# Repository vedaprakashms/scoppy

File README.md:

# scoppy
PI Pico ossciloscope using simple components

The project contains multiple directory, each with its own kind of Scopy, i.e Surface mountable, through hole, etc...

The Directory names are self explanatory. 

# IMAGES

## Scoppy SMD Single sided PCB

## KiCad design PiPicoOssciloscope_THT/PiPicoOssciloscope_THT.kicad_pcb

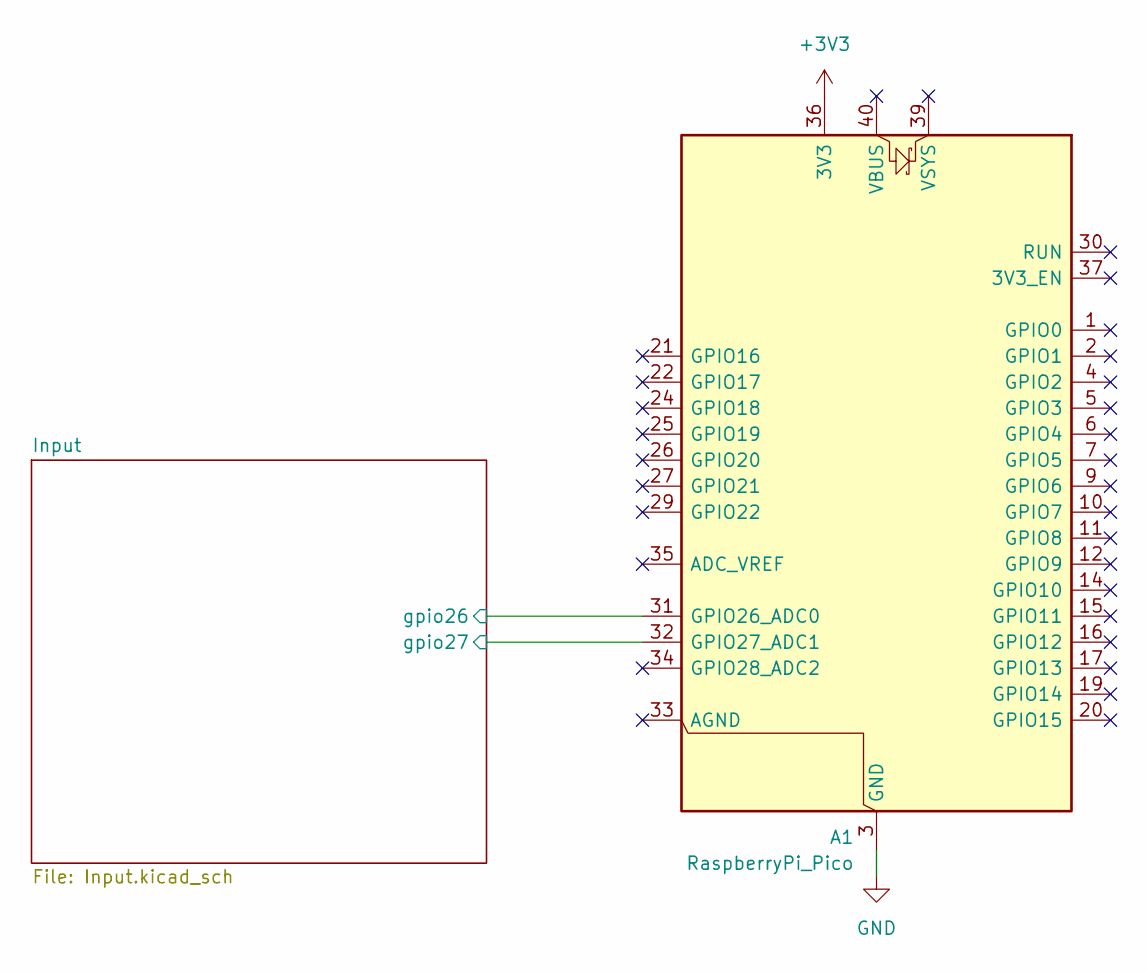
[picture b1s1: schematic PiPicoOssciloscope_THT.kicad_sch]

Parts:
A1: RaspberryPi_Pico; RaspberryPi_Pico_Common_THT

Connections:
+3V3: A1.36 (3V3); also elsewhere on the board
/Input/gpio26: A1.31 (GPIO26_ADC0); also elsewhere on the board
/Input/gpio27: A1.32 (GPIO27_ADC1); also elsewhere on the board
GND: A1.3 (GND), A1.8 (GND), A1.13 (GND), A1.18 (GND), A1.23 (GND), A1.28 (GND), A1.38 (GND); also elsewhere on the board

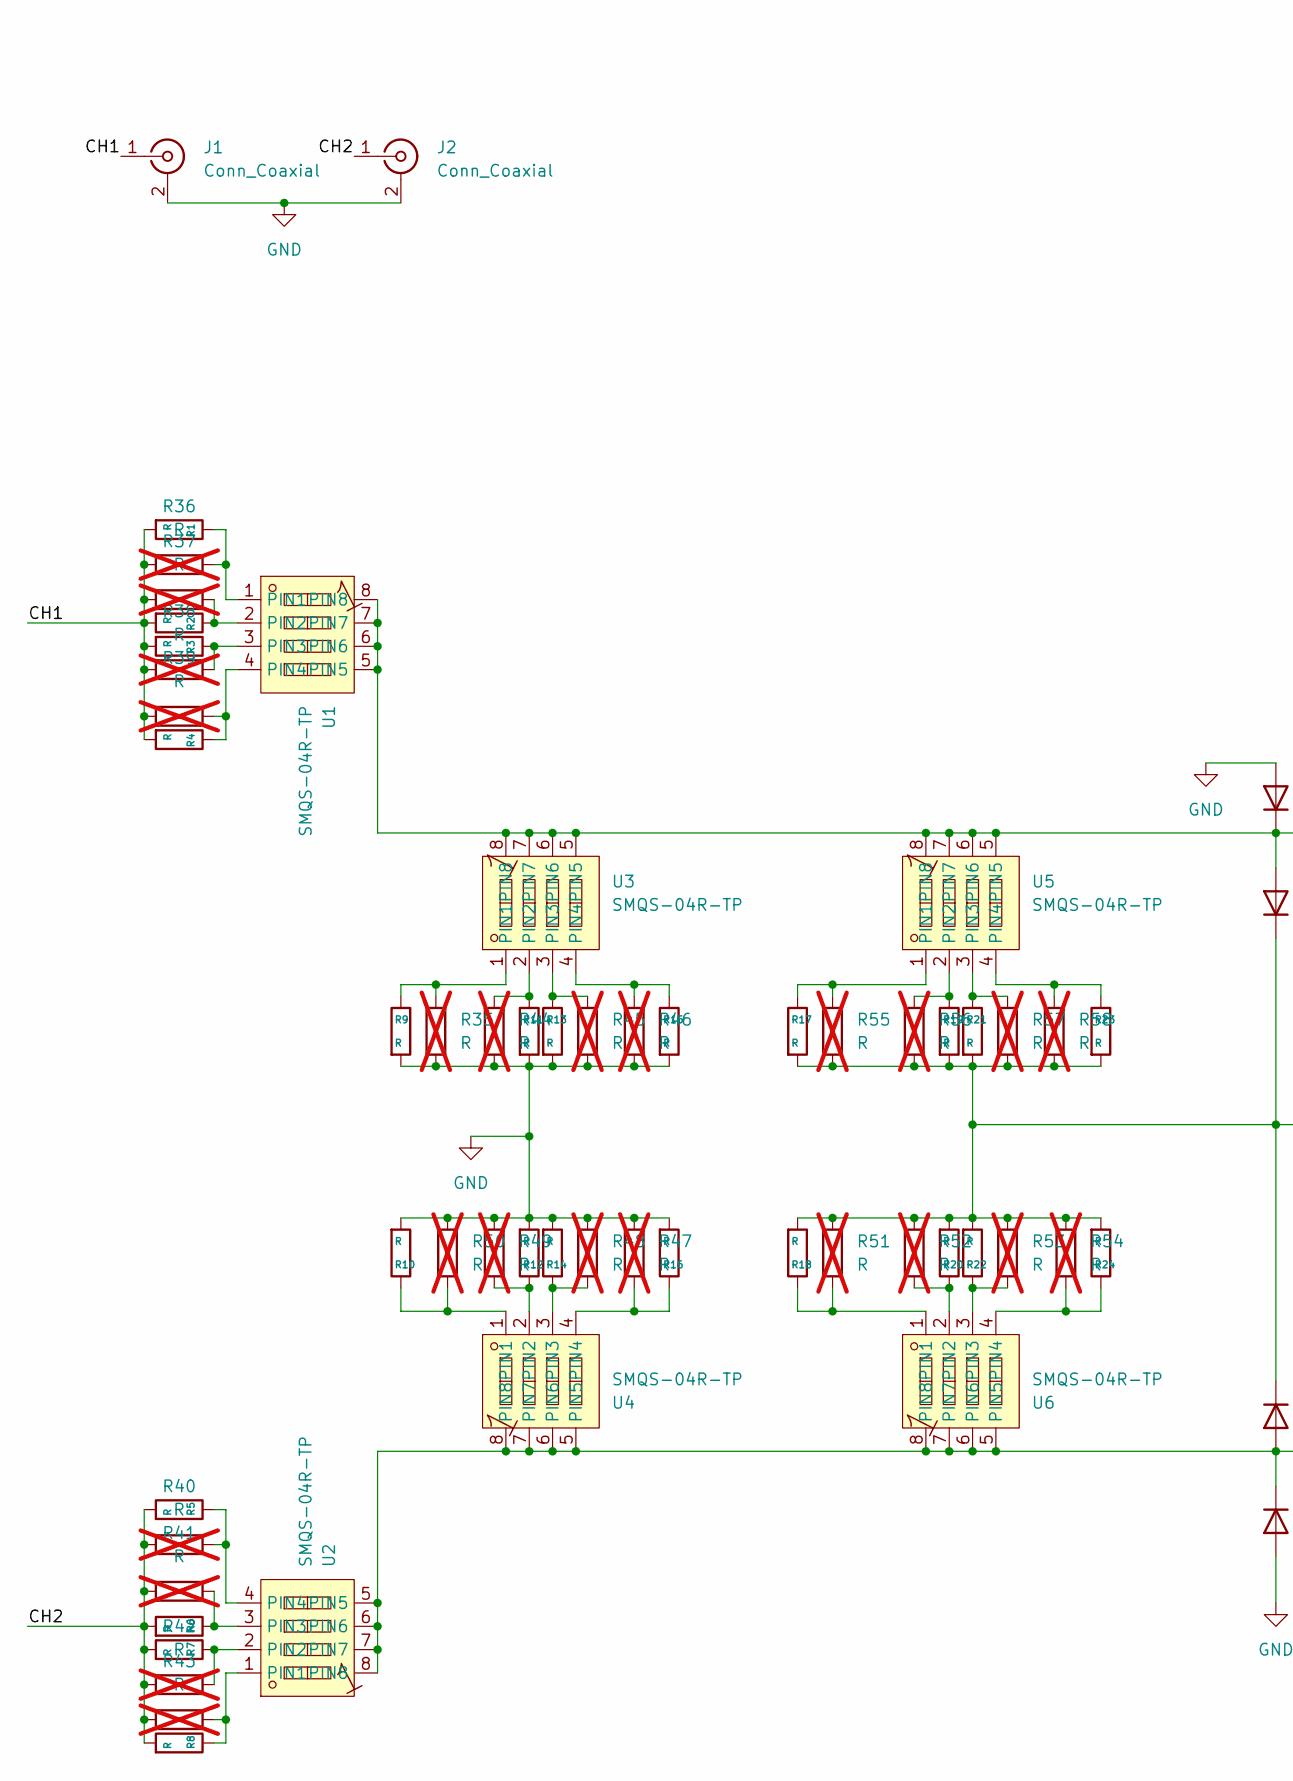
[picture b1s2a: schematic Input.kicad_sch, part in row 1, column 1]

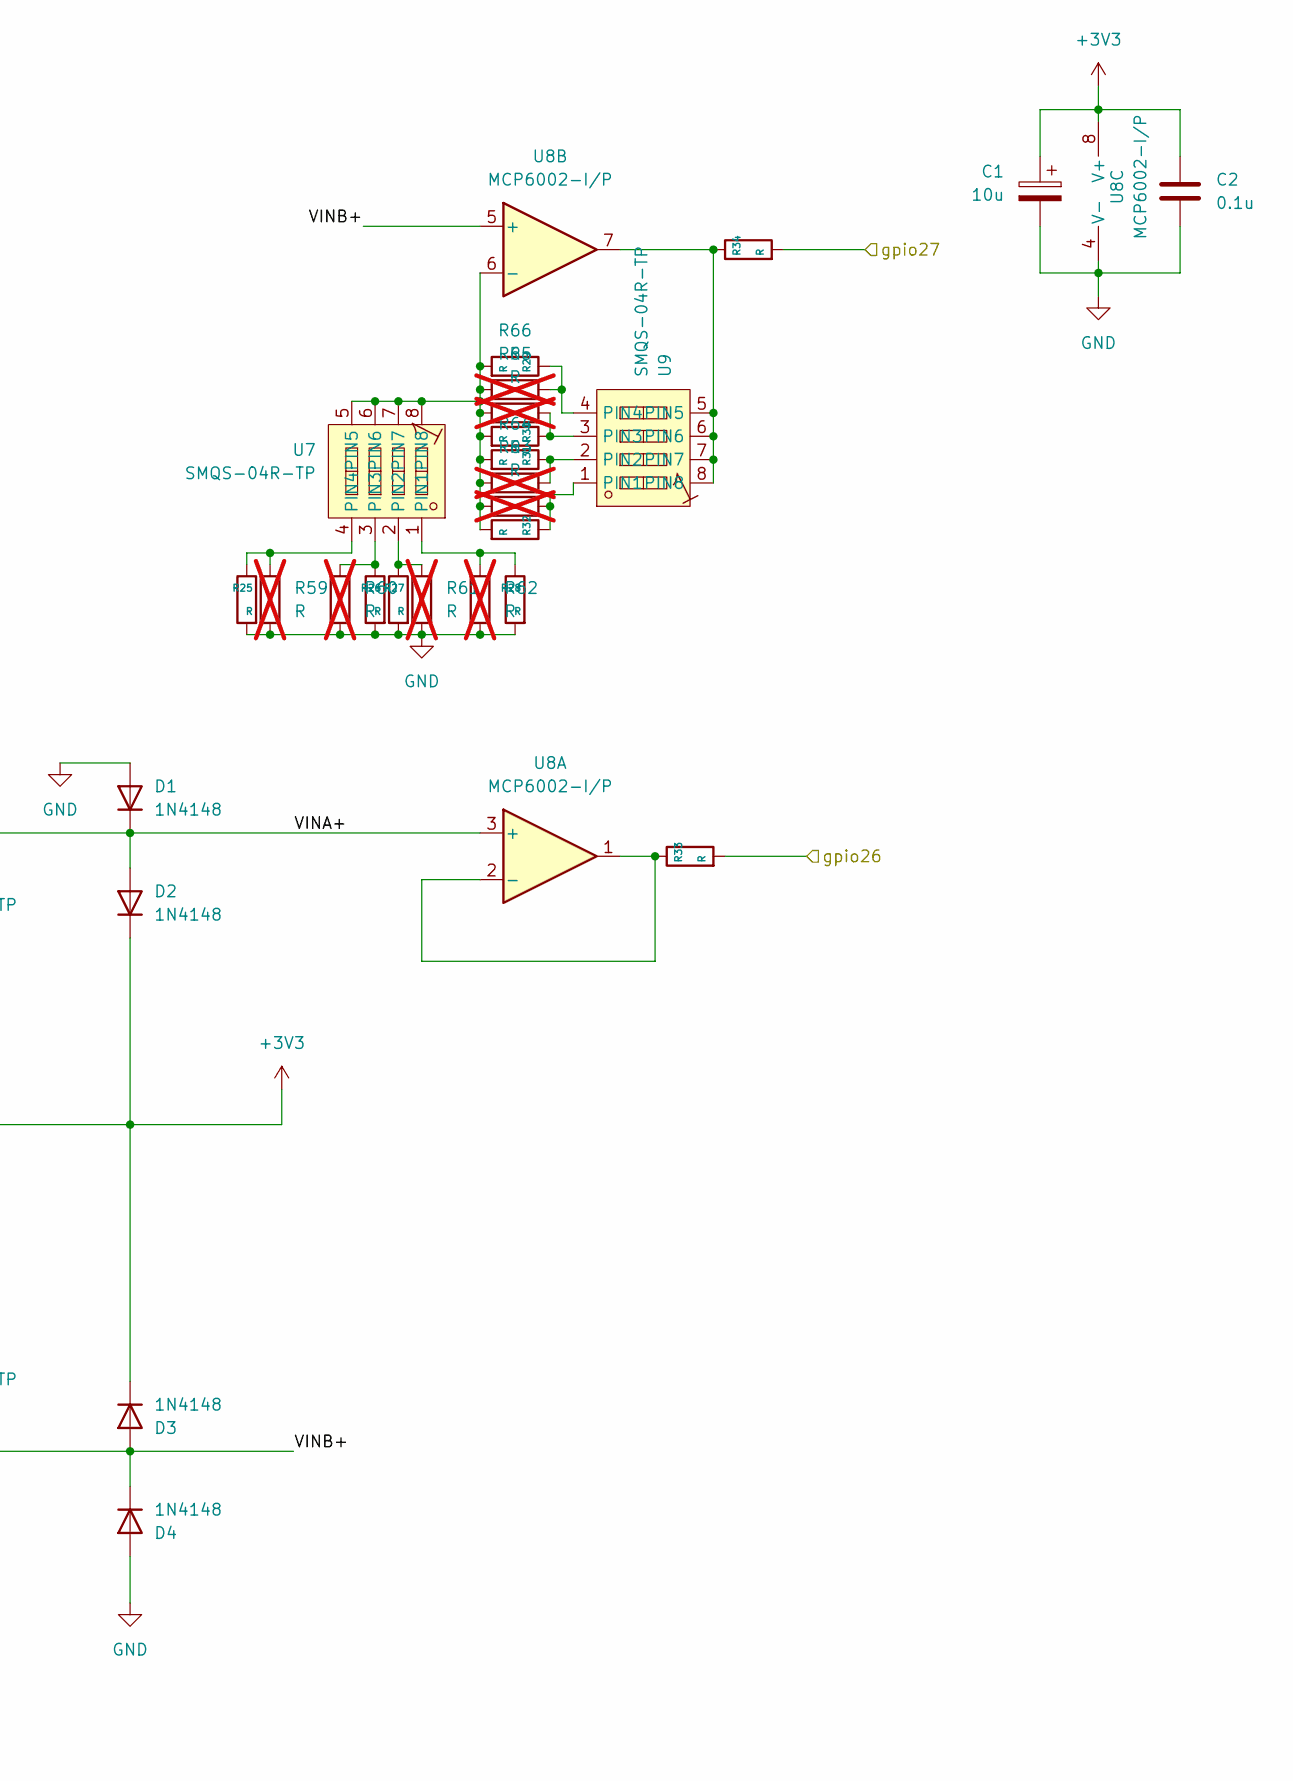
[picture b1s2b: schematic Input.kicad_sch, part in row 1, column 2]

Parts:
C1: 10u; CP_Radial_D10.0mm_P2.50mm
C2: 0.1u; C_Disc_D3.0mm_W1.6mm_P2.50mm
D1, D2, D3, D4: 1N4148; D_DO-35_SOD27_P7.62mm_Horizontal
J1, J2: Conn_Coaxial; BNC_Amphenol_B6252HB-NPP3G-50_Horizontal
R1, R2, R3, R4, R5, R6, R7, R8, R9, R10, R11, R12, R13, R14, R15, R16, R17, R18, R19, R20, R21, R22, R23, R24, R25, R26, R27, R28, R29, R30, R31, R32, R33, R34: R; R_Axial_DIN0204_L3.6mm_D1.6mm_P7.62mm_Horizontal
R35, R36, R37, R38, R39, R40, R41, R42, R43, R44, R45, R46, R47, R48, R49, R50, R51, R52, R53, R54, R55, R56, R57, R58, R59, R60, R61, R62, R63, R64, R65, R66: R; R_0805_2012Metric_Pad1.20x1.40mm_HandSolder; not fitted
U1, U2, U3, U4, U5, U6, U7, U9: SMQS-04R-TP; SW-TH_8P-P2.54_SMQS-04R-TP; MPN SMQS-04R-TP; LCSC Part C5299505
U8: MCP6002-I/P; DIP-8_W7.62mm_Socket_LongPads

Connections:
+3V3: C1.1, C2.1, D2.1 (K), D3.1 (K), R17.2, R18.2, R19.2, R20.2, R21.2, R22.2, R23.2, R24.2, R51.1, R52.1, R53.1, R54.1, R55.2, R56.2, R57.2, R58.2, U8.8 (V+); also elsewhere on the board
/Input/CH1: J1.1 (In), R1.2, R2.2, R3.2, R4.2, R36.1, R37.1, R38.1, R39.1
/Input/CH2: J2.1 (In), R5.2, R6.2, R7.2, R8.2, R40.1, R41.1, R42.1, R43.1
/Input/VINA+: D1.1 (K), D2.2 (A), U1.5 (PIN5), U1.6 (PIN6), U1.7 (PIN7), U1.8 (PIN8), U3.5 (PIN5), U3.6 (PIN6), U3.7 (PIN7), U3.8 (PIN8), U5.5 (PIN5), U5.6 (PIN6), U5.7 (PIN7), U5.8 (PIN8), U8.3 (+)
/Input/VINB+: D3.2 (A), D4.1 (K), U2.5 (PIN5), U2.6 (PIN6), U2.7 (PIN7), U2.8 (PIN8), U4.5 (PIN5), U4.6 (PIN6), U4.7 (PIN7), U4.8 (PIN8), U6.5 (PIN5), U6.6 (PIN6), U6.7 (PIN7), U6.8 (PIN8), U8.5 (+)
/Input/gpio26: R33.2; also elsewhere on the board
/Input/gpio27: R34.2; also elsewhere on the board
GND: C1.2, C2.2, D1.2 (A), D4.2 (A), J1.2 (Ext), J2.2 (Ext), R9.2, R10.2, R11.2, R12.2, R13.2, R14.2, R15.2, R16.2, R25.2, R26.2, R27.2, R28.2, R35.2, R44.2, R45.2, R46.2, R47.1, R48.1, R49.1, R50.1, R59.2, R60.2, R61.2, R62.2, U8.4 (V-); also elsewhere on the board
unnamed: R1.1, R36.2, U1.1 (PIN1)
unnamed: R2.1, R37.2, U1.2 (PIN2)
unnamed: R3.1, R38.2, U1.3 (PIN3)
unnamed: R4.1, R39.2, U1.4 (PIN4)
unnamed: R8.1, R43.2, U2.1 (PIN1)
unnamed: R7.1, R42.2, U2.2 (PIN2)
unnamed: R6.1, R41.2, U2.3 (PIN3)
unnamed: R5.1, R40.2, U2.4 (PIN4)
unnamed: R9.1, R35.1, U3.1 (PIN1)
unnamed: R11.1, R44.1, U3.2 (PIN2)
unnamed: R13.1, R45.1, U3.3 (PIN3)
unnamed: R15.1, R46.1, U3.4 (PIN4)
unnamed: R10.1, R50.2, U4.1 (PIN1)
unnamed: R12.1, R49.2, U4.2 (PIN2)
unnamed: R14.1, R48.2, U4.3 (PIN3)
unnamed: R16.1, R47.2, U4.4 (PIN4)
unnamed: R17.1, R55.1, U5.1 (PIN1)
unnamed: R19.1, R56.1, U5.2 (PIN2)
unnamed: R21.1, R57.1, U5.3 (PIN3)
unnamed: R23.1, R58.1, U5.4 (PIN4)
unnamed: R18.1, R51.2, U6.1 (PIN1)
unnamed: R20.1, R52.2, U6.2 (PIN2)
unnamed: R22.1, R53.2, U6.3 (PIN3)
unnamed: R24.1, R54.2, U6.4 (PIN4)
unnamed: R28.1, R62.1, U7.1 (PIN1)
unnamed: R27.1, R61.1, U7.2 (PIN2)
unnamed: R26.1, R60.1, U7.3 (PIN3)
unnamed: R25.1, R59.1, U7.4 (PIN4)
unnamed: R29.2, R30.2, R31.2, R32.2, R63.1, R64.1, R65.1, R66.1, U7.5 (PIN5), U7.6 (PIN6), U7.7 (PIN7), U7.8 (PIN8), U8.6 (-)
unnamed: R33.1, U8.1, U8.2 (-)
unnamed: R32.1, R63.2, U9.1 (PIN1)
unnamed: R31.1, R64.2, U9.2 (PIN2)
unnamed: R30.1, R65.2, U9.3 (PIN3)
unnamed: R29.1, R66.2, U9.4 (PIN4)
unnamed: R34.1, U8.7, U9.5 (PIN5), U9.6 (PIN6), U9.7 (PIN7), U9.8 (PIN8)

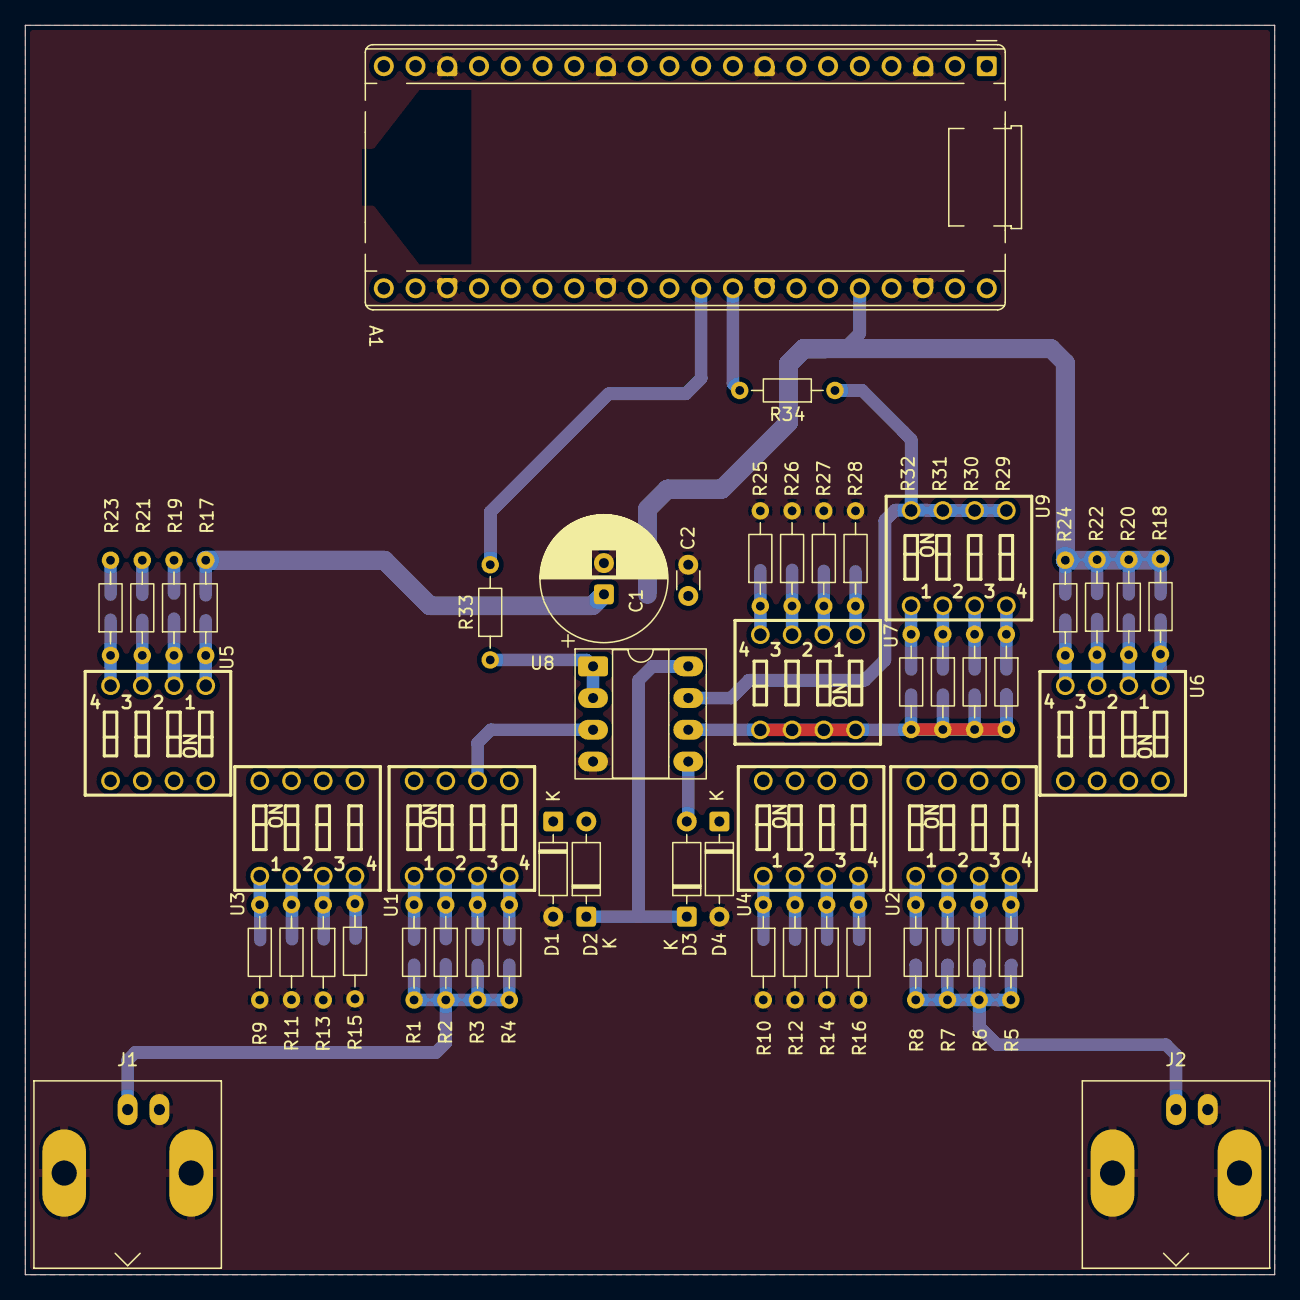
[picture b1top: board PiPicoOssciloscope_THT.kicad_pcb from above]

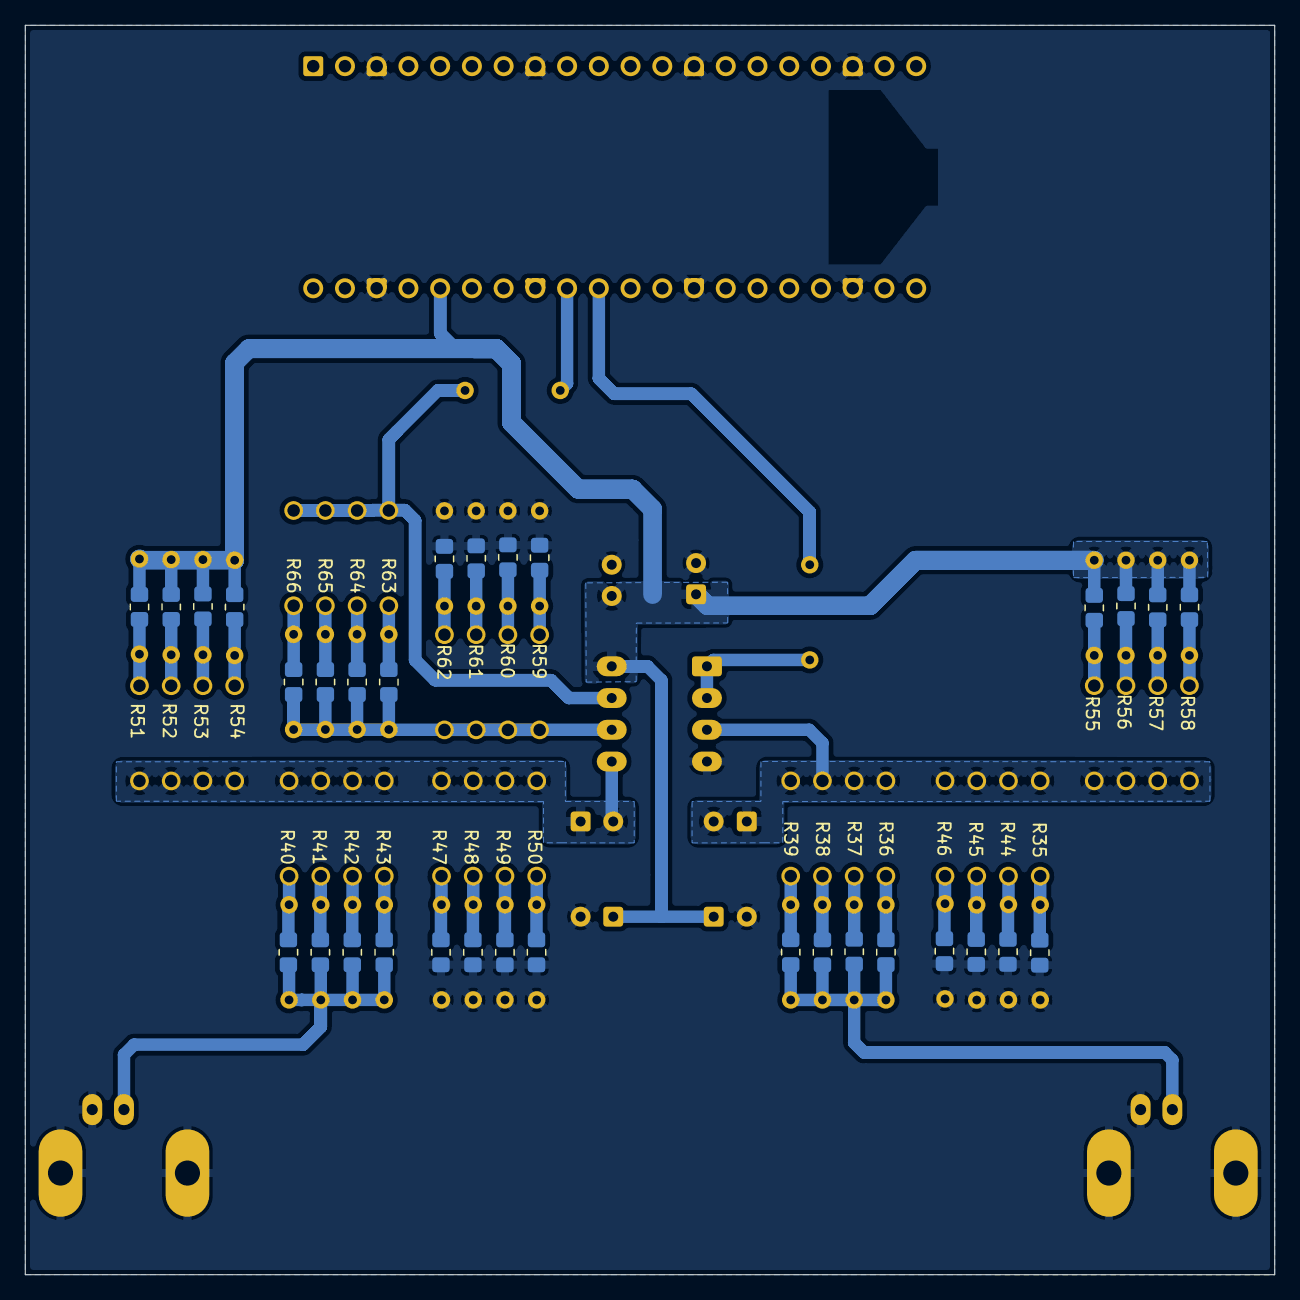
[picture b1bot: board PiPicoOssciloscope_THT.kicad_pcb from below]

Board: 2 copper layers, 100.0 x 100.0 mm, 84 parts (32 on the bottom side), 43 nets.

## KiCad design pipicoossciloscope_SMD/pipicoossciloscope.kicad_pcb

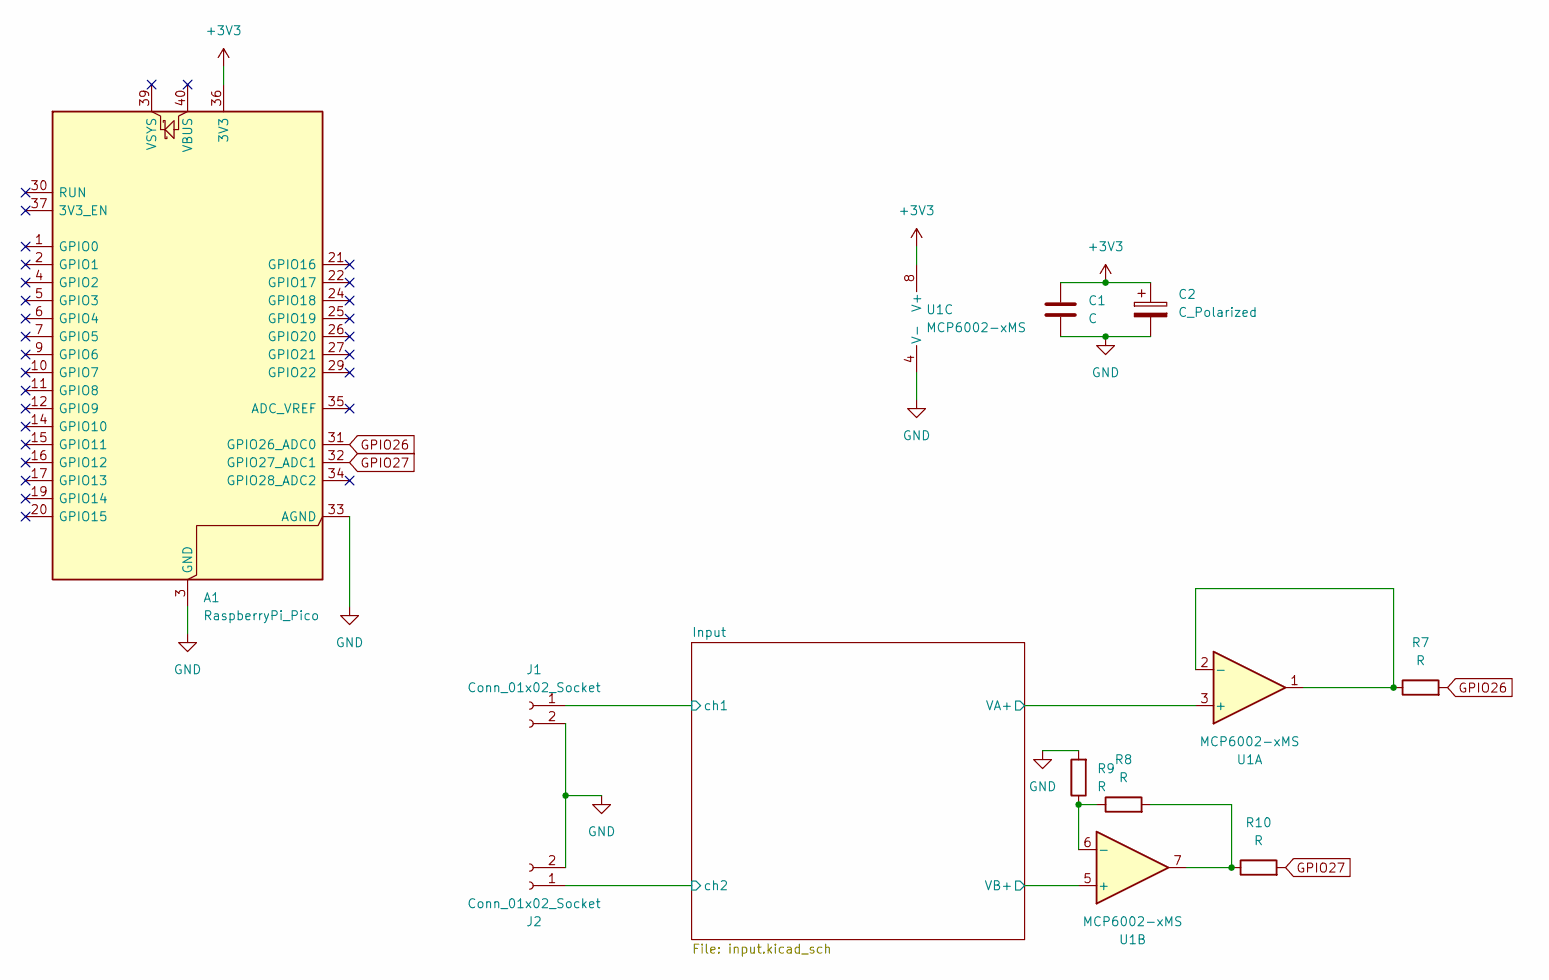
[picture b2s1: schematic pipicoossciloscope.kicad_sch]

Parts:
A1: RaspberryPi_Pico; RaspberryPi_Pico_Common_Unspecified
C1: C; C_1206_3216Metric_Pad1.33x1.80mm_HandSolder
C2: C_Polarized; CP_Elec_4x5.4
J1, J2: Conn_01x02_Socket; PinSocket_1x02_P2.54mm_Vertical
R7, R8, R9, R10: R; R_1206_3216Metric_Pad1.30x1.75mm_HandSolder
U1: MCP6002-xMS; MSOP-8_3x3mm_P0.65mm

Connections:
+3V3: A1.36 (3V3), C1.1, C2.1, U1.8 (V+); also elsewhere on the board
/Input/VA+: U1.3 (+); also elsewhere on the board
/Input/VB+: U1.5 (+); also elsewhere on the board
/Input/ch1: J1.1; also elsewhere on the board
/Input/ch2: J2.1; also elsewhere on the board
GND: A1.3 (GND), A1.8 (GND), A1.13 (GND), A1.18 (GND), A1.23 (GND), A1.28 (GND), A1.33 (AGND), A1.38 (GND), C1.2, C2.2, J1.2, J2.2, R9.2, U1.4 (V-); also elsewhere on the board
GPIO26: A1.31 (GPIO26_ADC0), R7.2
GPIO27: A1.32 (GPIO27_ADC1), R10.2
unnamed: R8.2, R10.1, U1.7
unnamed: R7.1, U1.1, U1.2 (-)
unnamed: R8.1, R9.1, U1.6 (-)

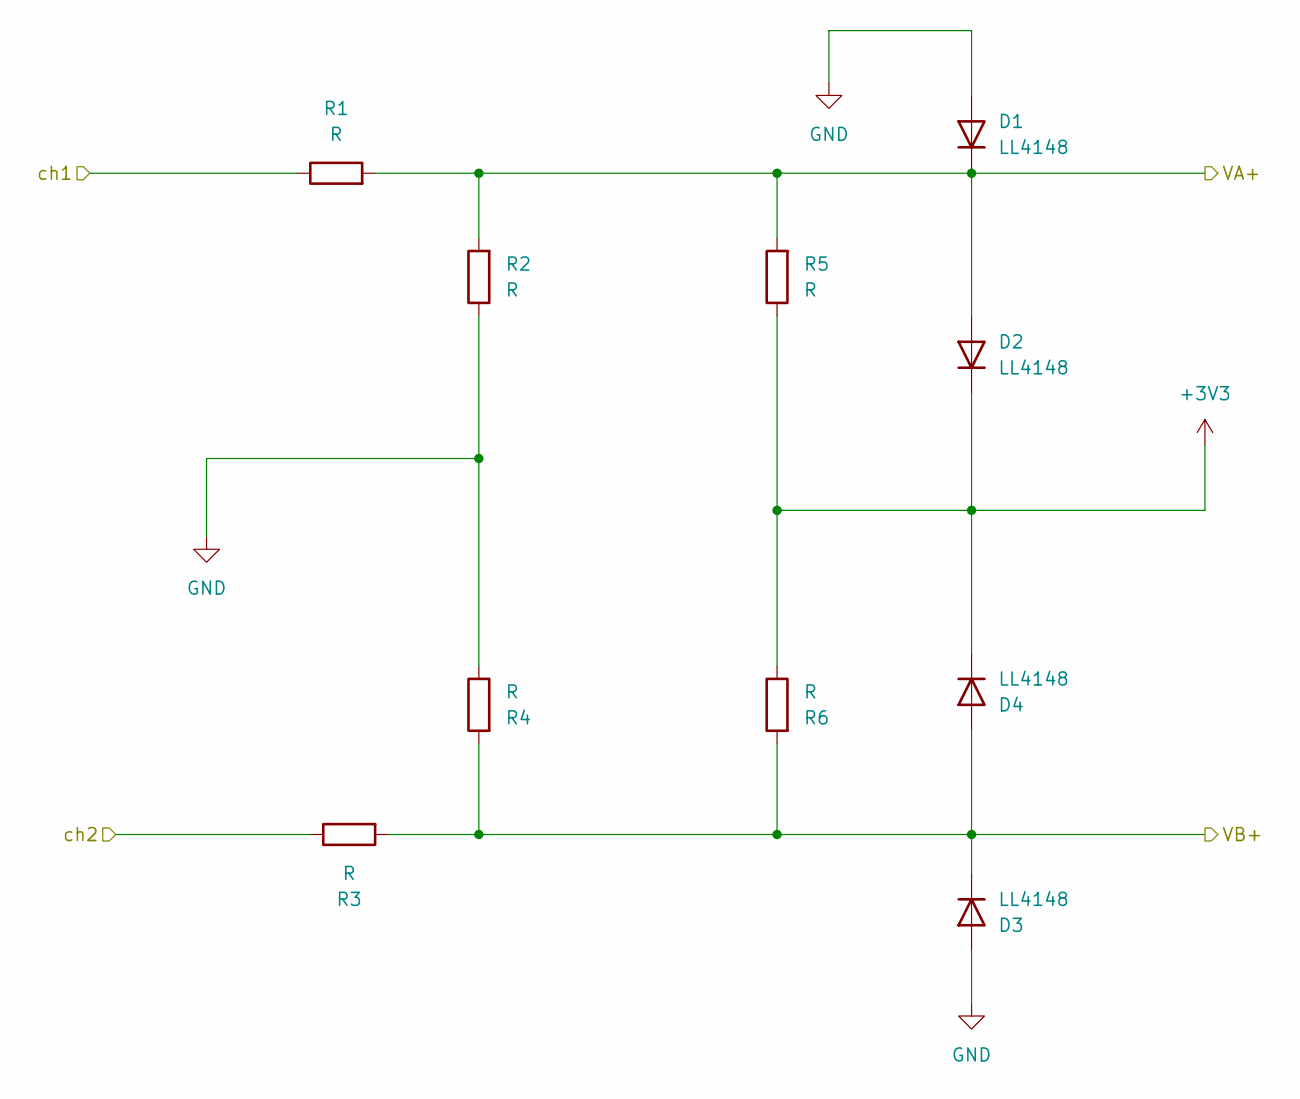
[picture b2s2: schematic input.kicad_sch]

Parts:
D1, D2, D3, D4: LL4148; D_MiniMELF_Handsoldering
R1, R2, R3, R4, R5, R6: R; R_1206_3216Metric_Pad1.30x1.75mm_HandSolder

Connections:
+3V3: D2.1 (K), D4.1 (K), R5.1, R6.1; also elsewhere on the board
/Input/VA+: D1.1 (K), D2.2 (A), R1.2, R2.2, R5.2; also elsewhere on the board
/Input/VB+: D3.1 (K), D4.2 (A), R3.2, R4.2, R6.2; also elsewhere on the board
/Input/ch1: R1.1; also elsewhere on the board
/Input/ch2: R3.1; also elsewhere on the board
GND: D1.2 (A), D3.2 (A), R2.1, R4.1; also elsewhere on the board

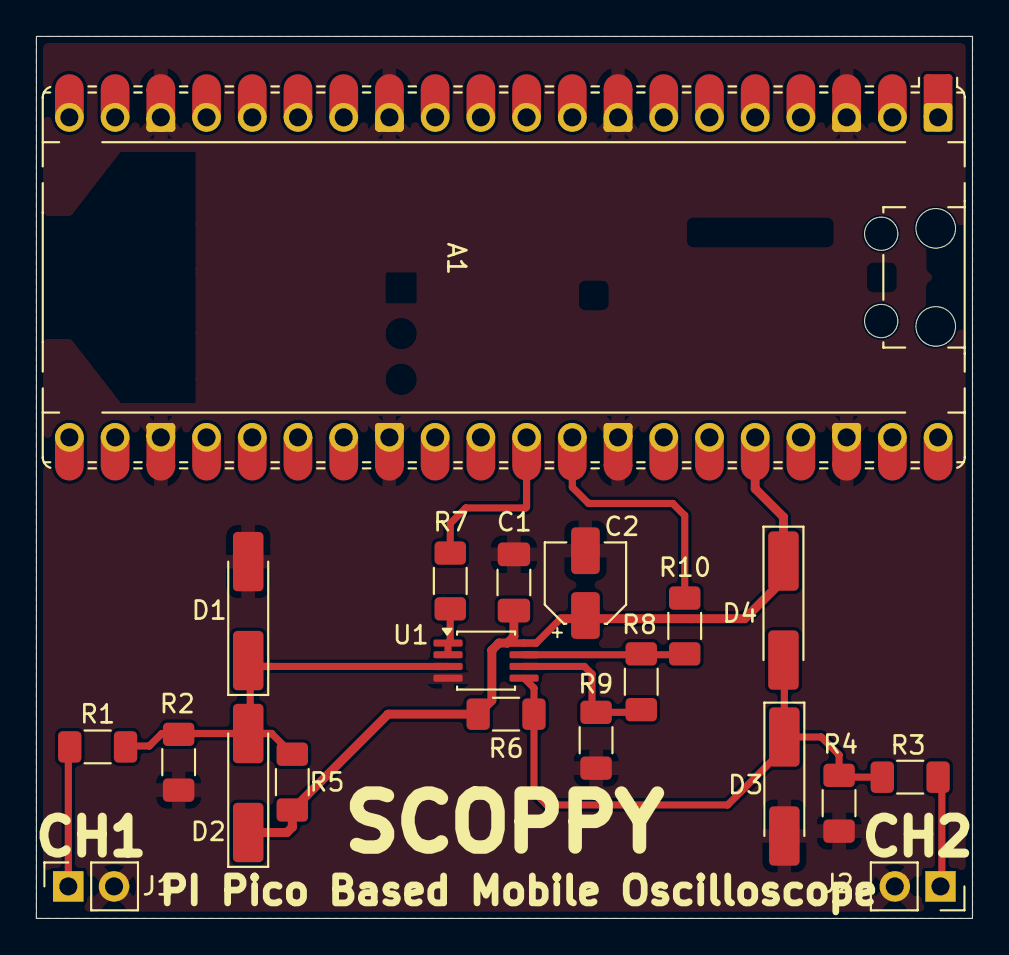
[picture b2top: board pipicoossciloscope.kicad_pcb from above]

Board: 2 copper layers, 52.0 x 49.0 mm, 20 parts (0 on the bottom side), 11 nets.

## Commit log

2026-06-13 SMD scopy update.
2026-06-13 added images to readme
2026-06-13 THT updated
2026-06-14 updated the bnc connector
